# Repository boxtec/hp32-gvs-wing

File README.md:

# hp32-gvs-wing
GVS Wing Kit for HelvePic32

See http://helvepic32.net or http://helvepic32.org/ for more information.

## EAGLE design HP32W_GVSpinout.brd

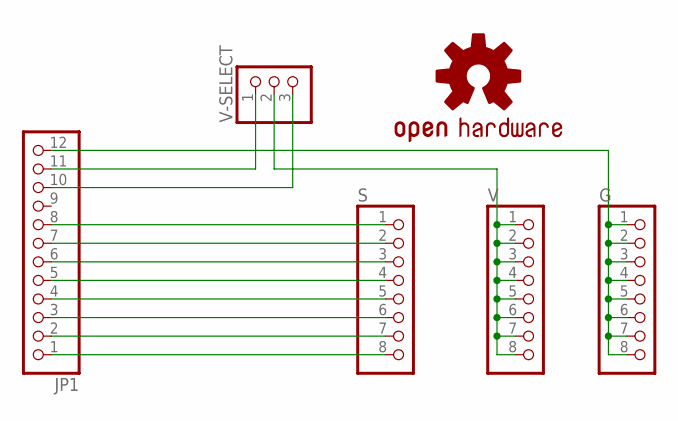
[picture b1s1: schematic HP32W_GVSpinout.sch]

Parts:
G: PINHD-1X8BIG; 1X08-BIG
JP1: PINHD-1X12-CB; 1X12-CB
LOGO1: OSHW-LOGOS; OSHW-LOGO-S
S: PINHD-1X8BIG; 1X08-BIG
V: PINHD-1X8BIG; 1X08-BIG
V-SELECT: PINHD-1X3; 1X03

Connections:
unnamed: JP1.1, S.8
unnamed: G.1, G.2, G.3, G.4, G.5, G.6, G.7, G.8, JP1.12
unnamed: JP1.2, S.7
unnamed: JP1.3, S.6
unnamed: JP1.4, S.5
unnamed: JP1.5, S.4
unnamed: JP1.6, S.3
unnamed: JP1.7, S.2
unnamed: JP1.8, S.1
unnamed: JP1.11, V-SELECT.1
unnamed: JP1.10, V-SELECT.3
unnamed: V.1, V.2, V.3, V.4, V.5, V.6, V.7, V.8, V-SELECT.2

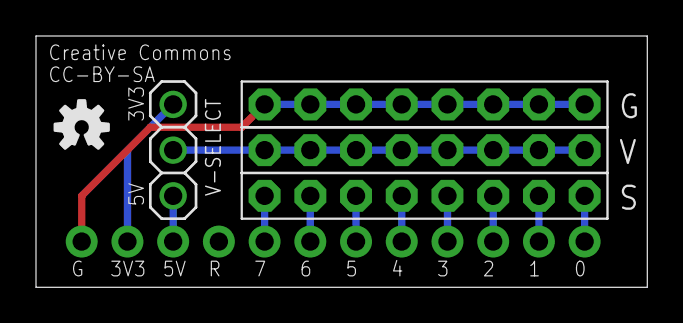
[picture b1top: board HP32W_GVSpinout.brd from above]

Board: 2 copper layers, 34.0 x 14.0 mm, 6 parts (0 on the bottom side), 12 nets.

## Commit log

2015-11-11 Initial git import

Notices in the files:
HP32W_GVSpinout.brd:
Creative Commons
CC-BY-SA
parts and their libraries:
SparkFun-Aesthetics: Licensing: Creative Commons ShareAlike 4.0 International - https://creativecommons.org/licenses/by-sa/4.0
